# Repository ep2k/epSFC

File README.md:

# epSFC - SUPER Famicom Emulator on an FPGA

epSFC is an implementation of Nintendo's __SUPER Famicom (SFC)__ written in SystemVerilog.
It works on an FPGA board with a board for connection to SFC cartridges.

The operation has been confirmed with Terasic DE0-CV Board.

<br>

")

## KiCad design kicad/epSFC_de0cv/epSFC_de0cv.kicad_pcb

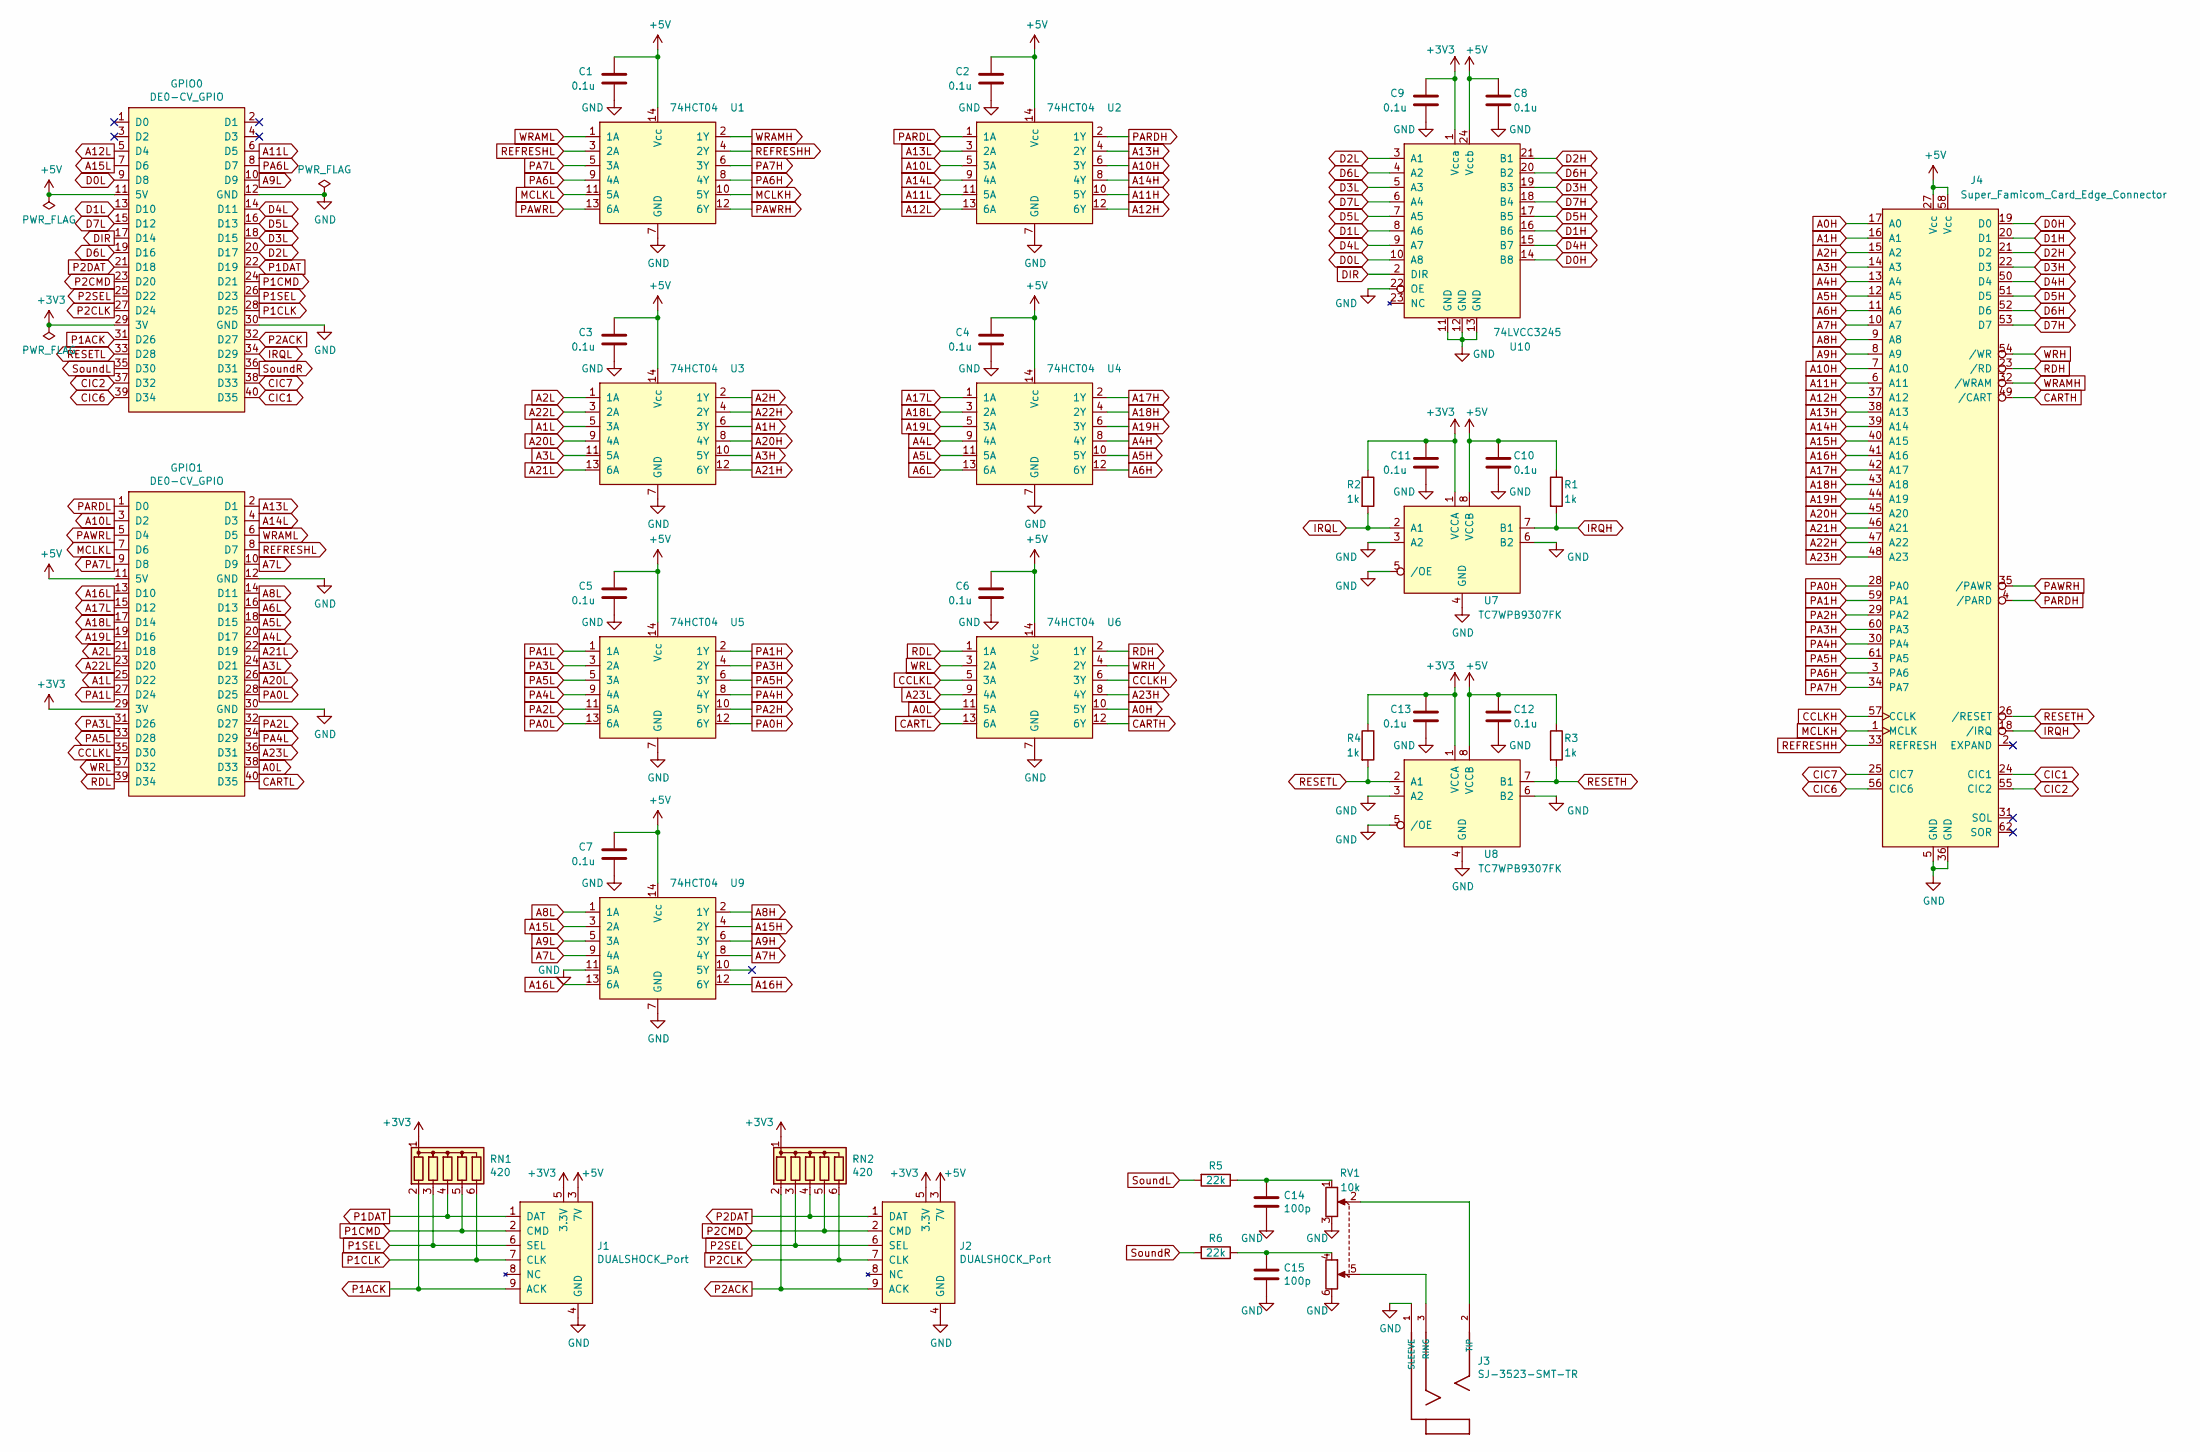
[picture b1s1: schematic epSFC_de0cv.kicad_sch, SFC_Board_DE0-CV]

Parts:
C1, C2, C3, C4, C5, C6, C7, C8, C9, C10, C11, C12, C13: 0.1u; C_1206_3216Metric_Pad1.33x1.80mm_HandSolder
C14, C15: 100p; C_1206_3216Metric_Pad1.33x1.80mm_HandSolder
GPIO0, GPIO1: DE0-CV_GPIO; PinSocket_2x20_P2.54mm_Vertical_Back
J1, J2: DUALSHOCK_Port
J3: SJ-3523-SMT-TR; CUI_SJ-3523-SMT-TR
J4: Super_Famicom_Card_Edge_Connector; SuperFamicom_Card_Edge_Connector
R1, R2, R3, R4: 1k; R_1206_3216Metric_Pad1.30x1.75mm_HandSolder
R5, R6: 22k; R_1206_3216Metric_Pad1.30x1.75mm_HandSolder
RN1, RN2: 420; R_Array_SIP6
RV1: 10k; Potentiometer_Bourns_PTV112
U1, U2, U3, U4, U5, U6, U9: 74HCT04; SOIC-14_3.9x8.7mm_P1.27mm
U7, U8: TC7WPB9307FK; US8
U10: 74LVCC3245; SO-24_5.3x15mm_P1.27mm

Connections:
+3V3: C9.1, C11.1, C13.1, GPIO0.29 (3V), GPIO1.29 (3V), J1.5 (3.3V), J2.5 (3.3V), R2.1, R4.1, RN1.1 (common), RN2.1 (common), U7.1 (VCCA), U8.1 (VCCA), U10.1 (Vcca)
+5V: C1.1, C2.1, C3.1, C4.1, C5.1, C6.1, C7.1, C8.1, C10.1, C12.1, GPIO0.11 (5V), GPIO1.11 (5V), J1.3 (7V), J2.3 (7V), J4.27 (Vcc), J4.58 (Vcc), R1.1, R3.1, U1.14 (Vcc), U2.14 (Vcc), U3.14 (Vcc), U4.14 (Vcc), U5.14 (Vcc), U6.14 (Vcc), U7.8 (VCCB), U8.8 (VCCB), U9.14 (Vcc), U10.24 (Vccb)
A0H: J4.17 (A0), U6.10 (5Y)
A0L: GPIO1.38 (D33), U6.11 (5A)
A1H: J4.16 (A1), U3.6 (3Y)
A1L: GPIO1.25 (D22), U3.5 (3A)
A2H: J4.15 (A2), U3.2 (1Y)
A2L: GPIO1.21 (D18), U3.1 (1A)
A3H: J4.14 (A3), U3.10 (5Y)
A3L: GPIO1.24 (D21), U3.11 (5A)
A4H: J4.13 (A4), U4.8 (4Y)
A4L: GPIO1.20 (D17), U4.9 (4A)
A5H: J4.12 (A5), U4.10 (5Y)
A5L: GPIO1.18 (D15), U4.11 (5A)
A6H: J4.11 (A6), U4.12 (6Y)
A6L: GPIO1.16 (D13), U4.13 (6A)
A7H: J4.10 (A7), U9.8 (4Y)
A7L: GPIO1.10 (D9), U9.9 (4A)
A8H: J4.9 (A8), U9.2 (1Y)
A8L: GPIO1.14 (D11), U9.1 (1A)
A9H: J4.8 (A9), U9.6 (3Y)
A9L: GPIO0.10 (D9), U9.5 (3A)
A10H: J4.7 (A10), U2.6 (3Y)
A10L: GPIO1.3 (D2), U2.5 (3A)
A11H: J4.6 (A11), U2.10 (5Y)
A11L: GPIO0.6 (D5), U2.11 (5A)
A12H: J4.37 (A12), U2.12 (6Y)
A12L: GPIO0.5 (D4), U2.13 (6A)
A13H: J4.38 (A13), U2.4 (2Y)
A13L: GPIO1.2 (D1), U2.3 (2A)
A14H: J4.39 (A14), U2.8 (4Y)
A14L: GPIO1.4 (D3), U2.9 (4A)
A15H: J4.40 (A15), U9.4 (2Y)
A15L: GPIO0.7 (D6), U9.3 (2A)
A16H: J4.41 (A16), U9.12 (6Y)
A16L: GPIO1.13 (D10), U9.13 (6A)
A17H: J4.42 (A17), U4.2 (1Y)
A17L: GPIO1.15 (D12), U4.1 (1A)
A18H: J4.43 (A18), U4.4 (2Y)
A18L: GPIO1.17 (D14), U4.3 (2A)
A19H: J4.44 (A19), U4.6 (3Y)
A19L: GPIO1.19 (D16), U4.5 (3A)
A20H: J4.45 (A20), U3.8 (4Y)
A20L: GPIO1.26 (D23), U3.9 (4A)
A21H: J4.46 (A21), U3.12 (6Y)
A21L: GPIO1.22 (D19), U3.13 (6A)
A22H: J4.47 (A22), U3.4 (2Y)
A22L: GPIO1.23 (D20), U3.3 (2A)
A23H: J4.48 (A23), U6.8 (4Y)
A23L: GPIO1.36 (D31), U6.9 (4A)
CARTH: J4.49 (/CART), U6.12 (6Y)
CARTL: GPIO1.40 (D35), U6.13 (6A)
CCLKH: J4.57 (CCLK), U6.6 (3Y)
CCLKL: GPIO1.35 (D30), U6.5 (3A)
CIC1: GPIO0.40 (D35), J4.24 (CIC1)
CIC2: GPIO0.37 (D32), J4.55 (CIC2)
CIC6: GPIO0.39 (D34), J4.56 (CIC6)
CIC7: GPIO0.38 (D33), J4.25 (CIC7)
D0H: J4.19 (D0), U10.14 (B8)
D0L: GPIO0.9 (D8), U10.10 (A8)
D1H: J4.20 (D1), U10.16 (B6)
D1L: GPIO0.13 (D10), U10.8 (A6)
D2H: J4.21 (D2), U10.21 (B1)
D2L: GPIO0.20 (D17), U10.3 (A1)
D3H: J4.22 (D3), U10.19 (B3)
D3L: GPIO0.18 (D15), U10.5 (A3)
D4H: J4.50 (D4), U10.15 (B7)
D4L: GPIO0.14 (D11), U10.9 (A7)
D5H: J4.51 (D5), U10.17 (B5)
D5L: GPIO0.16 (D13), U10.7 (A5)
D6H: J4.52 (D6), U10.20 (B2)
D6L: GPIO0.19 (D16), U10.4 (A2)
D7H: J4.53 (D7), U10.18 (B4)
D7L: GPIO0.15 (D12), U10.6 (A4)
DIR: GPIO0.17 (D14), U10.2 (DIR)
GND: C1.2, C2.2, C3.2, C4.2, C5.2, C6.2, C7.2, C8.2, C9.2, C10.2, C11.2, C12.2, C13.2, C14.2, C15.2, GPIO0.12 (GND), GPIO0.30 (GND), GPIO1.12 (GND), GPIO1.30 (GND), J1.4 (GND), J2.4 (GND), J3.1 (SLEEVE), J4.5 (GND), J4.36 (GND), RV1.3, RV1.6, U1.7 (GND), U2.7 (GND), U3.7 (GND), U4.7 (GND), U5.7 (GND), U6.7 (GND), U7.3 (A2), U7.4 (GND), U7.5 (/OE), U7.6 (B2), U8.3 (A2), U8.4 (GND), U8.5 (/OE), U8.6 (B2), U9.7 (GND), U9.11 (5A), U10.11 (GND), U10.12 (GND), U10.13 (GND), U10.22 (OE)
IRQH: J4.18 (/IRQ), R1.2, U7.7 (B1)
IRQL: GPIO0.34 (D29), R2.2, U7.2 (A1)
MCLKH: J4.1 (MCLK), U1.10 (5Y)
MCLKL: GPIO1.7 (D6), U1.11 (5A)
unnamed: C14.1, R5.1, RV1.1
unnamed: C15.1, R6.1, RV1.4
unnamed: J3.3 (RING), RV1.5
unnamed: J3.2 (TIP), RV1.2
P1ACK: GPIO0.31 (D26), J1.9 (ACK), RN1.2 (R1)
P1CLK: GPIO0.28 (D25), J1.7 (CLK), RN1.6 (R5)
P1CMD: GPIO0.24 (D21), J1.2 (CMD), RN1.5 (R4)
P1DAT: GPIO0.22 (D19), J1.1 (DAT), RN1.4 (R3)
P1SEL: GPIO0.26 (D23), J1.6 (SEL), RN1.3 (R2)
P2ACK: GPIO0.32 (D27), J2.9 (ACK), RN2.2 (R1)
P2CLK: GPIO0.27 (D24), J2.7 (CLK), RN2.6 (R5)
P2CMD: GPIO0.23 (D20), J2.2 (CMD), RN2.5 (R4)
P2DAT: GPIO0.21 (D18), J2.1 (DAT), RN2.4 (R3)
P2SEL: GPIO0.25 (D22), J2.6 (SEL), RN2.3 (R2)
PA0H: J4.28 (PA0), U5.12 (6Y)
PA0L: GPIO1.28 (D25), U5.13 (6A)
PA1H: J4.59 (PA1), U5.2 (1Y)
PA1L: GPIO1.27 (D24), U5.1 (1A)
PA2H: J4.29 (PA2), U5.10 (5Y)
PA2L: GPIO1.32 (D27), U5.11 (5A)
PA3H: J4.60 (PA3), U5.4 (2Y)
PA3L: GPIO1.31 (D26), U5.3 (2A)
PA4H: J4.30 (PA4), U5.8 (4Y)
PA4L: GPIO1.34 (D29), U5.9 (4A)
PA5H: J4.61 (PA5), U5.6 (3Y)
PA5L: GPIO1.33 (D28), U5.5 (3A)
PA6H: J4.3 (PA6), U1.8 (4Y)
PA6L: GPIO0.8 (D7), U1.9 (4A)
PA7H: J4.34 (PA7), U1.6 (3Y)
PA7L: GPIO1.9 (D8), U1.5 (3A)
PARDH: J4.4 (/PARD), U2.2 (1Y)
PARDL: GPIO1.1 (D0), U2.1 (1A)
PAWRH: J4.35 (/PAWR), U1.12 (6Y)
PAWRL: GPIO1.5 (D4), U1.13 (6A)
RDH: J4.23 (/RD), U6.2 (1Y)
RDL: GPIO1.39 (D34), U6.1 (1A)
REFRESHH: J4.33 (REFRESH), U1.4 (2Y)
REFRESHL: GPIO1.8 (D7), U1.3 (2A)
RESETH: J4.26 (/RESET), R3.2, U8.7 (B1)
RESETL: GPIO0.33 (D28), R4.2, U8.2 (A1)
SoundL: GPIO0.35 (D30), R5.2
SoundR: GPIO0.36 (D31), R6.2
WRAMH: J4.32 (/WRAM), U1.2 (1Y)
WRAML: GPIO1.6 (D5), U1.1 (1A)
WRH: J4.54 (/WR), U6.4 (2Y)
WRL: GPIO1.37 (D32), U6.3 (2A)

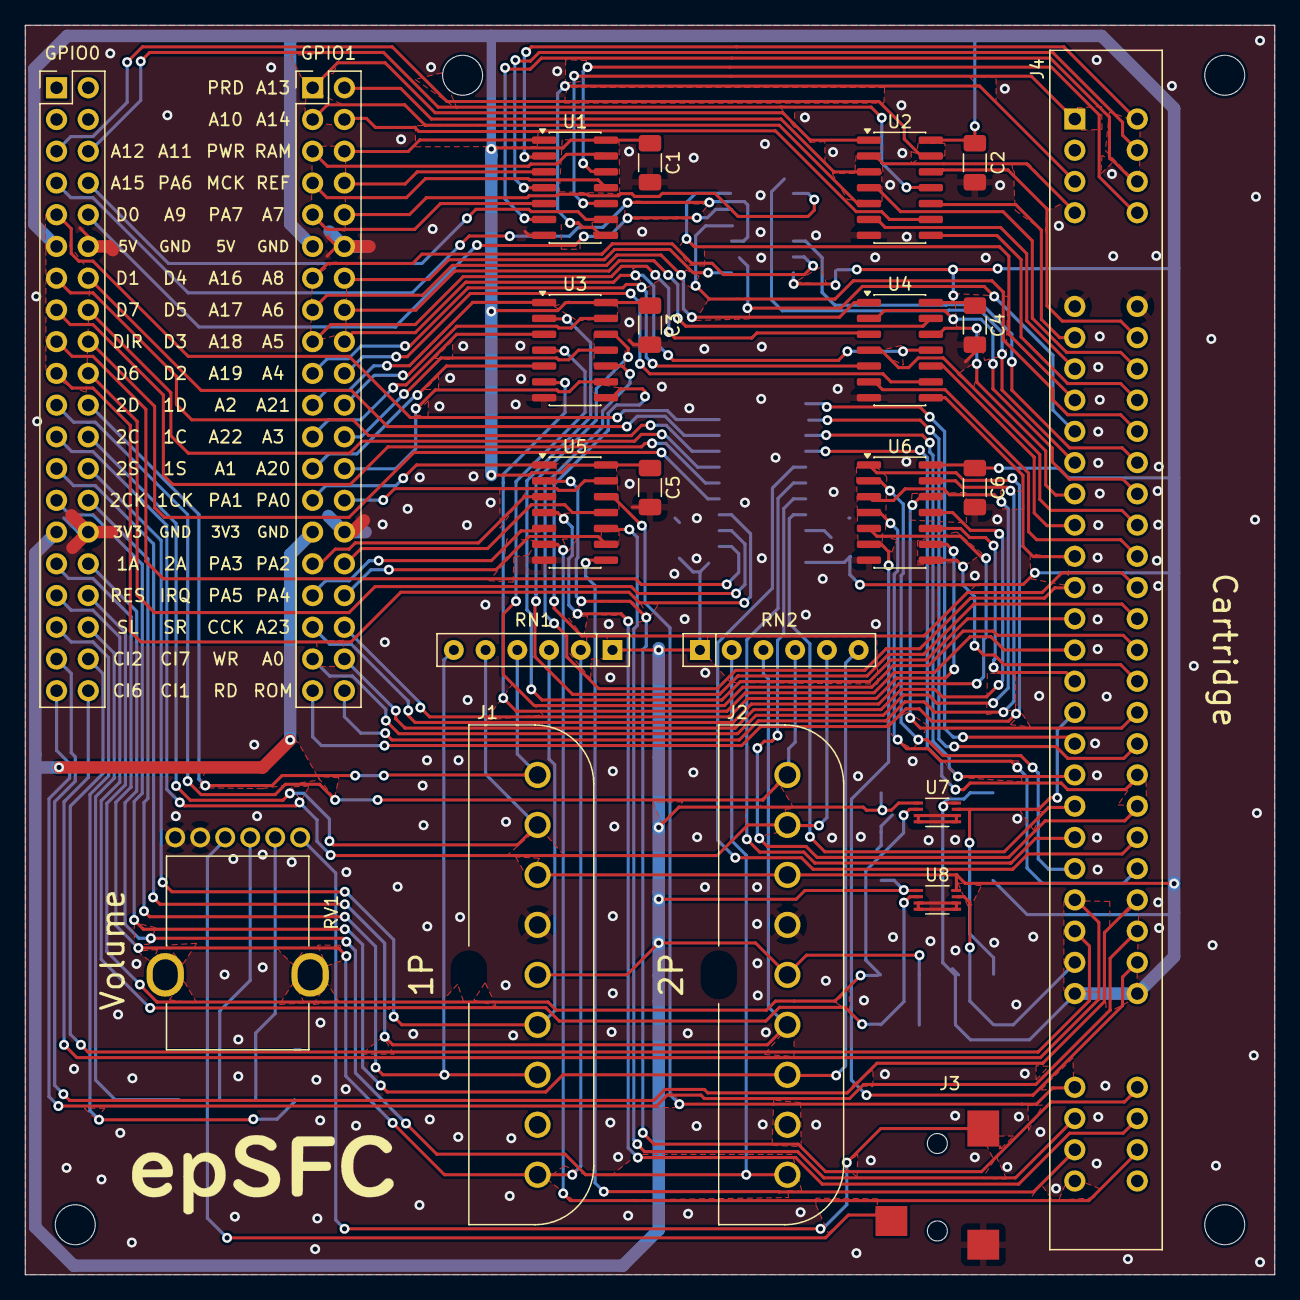
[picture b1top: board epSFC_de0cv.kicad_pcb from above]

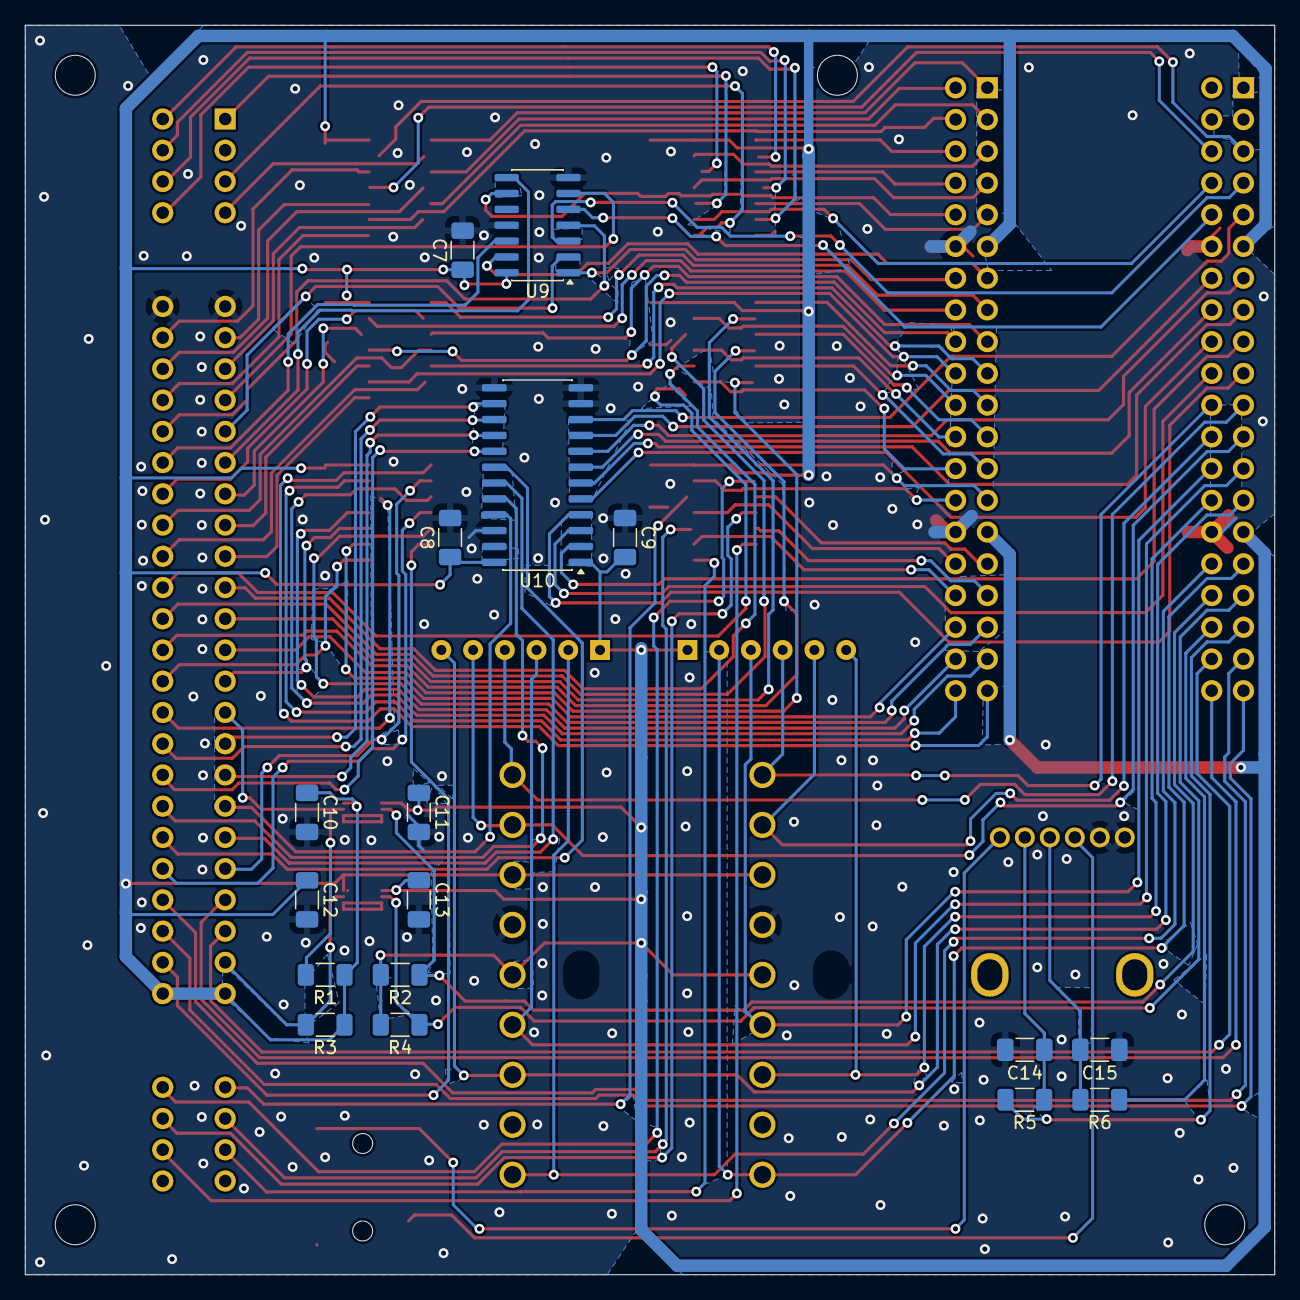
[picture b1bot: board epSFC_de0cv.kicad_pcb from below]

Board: 2 copper layers, 100.0 x 100.0 mm, 40 parts (17 on the bottom side), 126 nets.

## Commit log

2024-07-25 Initial empty commit
2024-07-26 feat: #2 CPUの追加
2024-07-26 feat: #2 PPUの追加
2024-07-26 feat: #2 APUの追加
2024-07-26 feat: #2 DMA Controllerの追加
2024-07-26 feat: #2 アドレスデコーダの追加
2024-07-26 feat: #2 WRAMの追加
2024-07-26 feat: #2 H/V Interrupt Controller の追加
2024-07-26 feat: #2 乗除算器の追加
2024-07-26 feat: #2 Memory Access Speed Counter の追加
2024-07-26 feat: #2 Joypadの追加
2024-07-26 feat: #2 Refresh信号コントローラーの追加
2024-07-26 feat: #2 Packageファイルの追加
2024-07-26 feat: #2 Console (SFC本体トップモジュール) の追加
2024-07-26 feat: #2 外部制御モジュールの追加
2024-07-26 feat: #2 Clock Generator の追加
2024-07-26 feat: #2 内部カートリッジの追加
2024-07-26 feat: #2 DE0-CV用トップモジュールの追加
2024-07-26 feat: #2 includeファイルテンプレートの追加
2024-07-26 feat: #2 ROMファイルの追加
2024-07-26 feat: #2 DE0-CV用制約ファイルの追加
2024-07-26 chore: #2 .gitignoreの追加
2024-07-26 style: #2 コメントの修正
2024-07-26 docs: #1 READMEの追加
2024-07-26 docs: #1 Create LICENSE
2024-07-27 fix: #7 cart_send信号を修正
2024-07-27 fix: #16 cart_reset_in, cart_irq_in をGPIO入力から反転
2024-07-27 feat: #16 consoleにcart_irq_inを入力
2024-07-29 feat: #3 ppuにbg7モジュール（空）を追加
2024-07-29 feat: #3 bg7に入力するx (x_bg7)を実装
2024-07-29 feat: #3 VRAMアドレスとしてbg7が出力したものを使用する期間を示す信号(bg7_period)を実装
2024-07-29 feat: #3 VRAMに入力するアドレスをL, Hで別の信号にする
2024-07-29 feat: #3 bgmode=7かつbg7_periodのときのVRAMアドレスをbg7が出力するものに変更
2024-07-29 feat: #3 Mode7の乗算を実装（乗算器*2，dot_ctrで乗算内容を変える）
2024-07-29 feat: #3 Mode7の乗算結果を一時保存するレジスタを作成
2024-07-29 feat: #3 bg7のVRAM.X, VRAM.Y計算を実装（dot_enでレジスタに保存）
2024-07-29 feat: #3 VRAMからのタイル番号，8bppピクセルの取得を実装
2024-07-30 feat: #3 Mode7ピクセル出力を実装
2024-07-30 feat: #3 Mode7でbg_pixelをbg7が出力したものとなるように変更
2024-07-30 feat: #3 Mode7をモザイクに対応
2024-07-30 feat: #3 pixel_mixerをMode7に対応
2024-07-30 fix: #3 スプライトのタイルフェッチタイミングに間に合わせるためにBG Mode 7を+7クロック早く動作させる（出力までシフトレジスタで結果を保持）
2024-07-31 fix: #22 refer_pal_selectorでdirect_colorを考慮するように修正
2024-08-02 fix: #14 BG 16x16pxタイルモードでのVRAMタイルデータアドレスを修正
2024-08-03 refactor: #23 モザイク信号をBG Mode 0-6と7で統一
2024-08-03 fix: #10 True H-RESでのVRAMタイルマップアドレス，タイルデータアドレスを修正
2024-08-03 fix: #10 True H-RESでのサブピクセルの処理を修正
2024-08-03 fix: #10 color_right/color_leftの選択にdot_ctr[1]ではなくh_ctr[1]を使用していた問題を修正
2024-08-04 fix: #15 ObjがVRAMアクセス中のCPUからのVRAM書き込みを無効化
2024-08-11 feat: #32 config.vhにCPUサイクル数テストの設定を追加
2024-08-12 feat: #32 65816 CPU に命令サイクル数テスト回路を追加
2024-08-12 feat: #32 SPC700 CPU に命令サイクル数テスト回路を追加
2024-08-12 fix: #34 MOV dp, dp にサイクル数が1多い問題を修正
2024-08-12 fix: #34 「MOV dp, dp」「MOV dp, #imm」でPSWを更新しないように修正
2025-11-02 feat: #37 .gitignoreにKiCad関連ファイルを追記
2025-11-02 feat: #37 カートリッジ接続基板のKiCadデータを追加
